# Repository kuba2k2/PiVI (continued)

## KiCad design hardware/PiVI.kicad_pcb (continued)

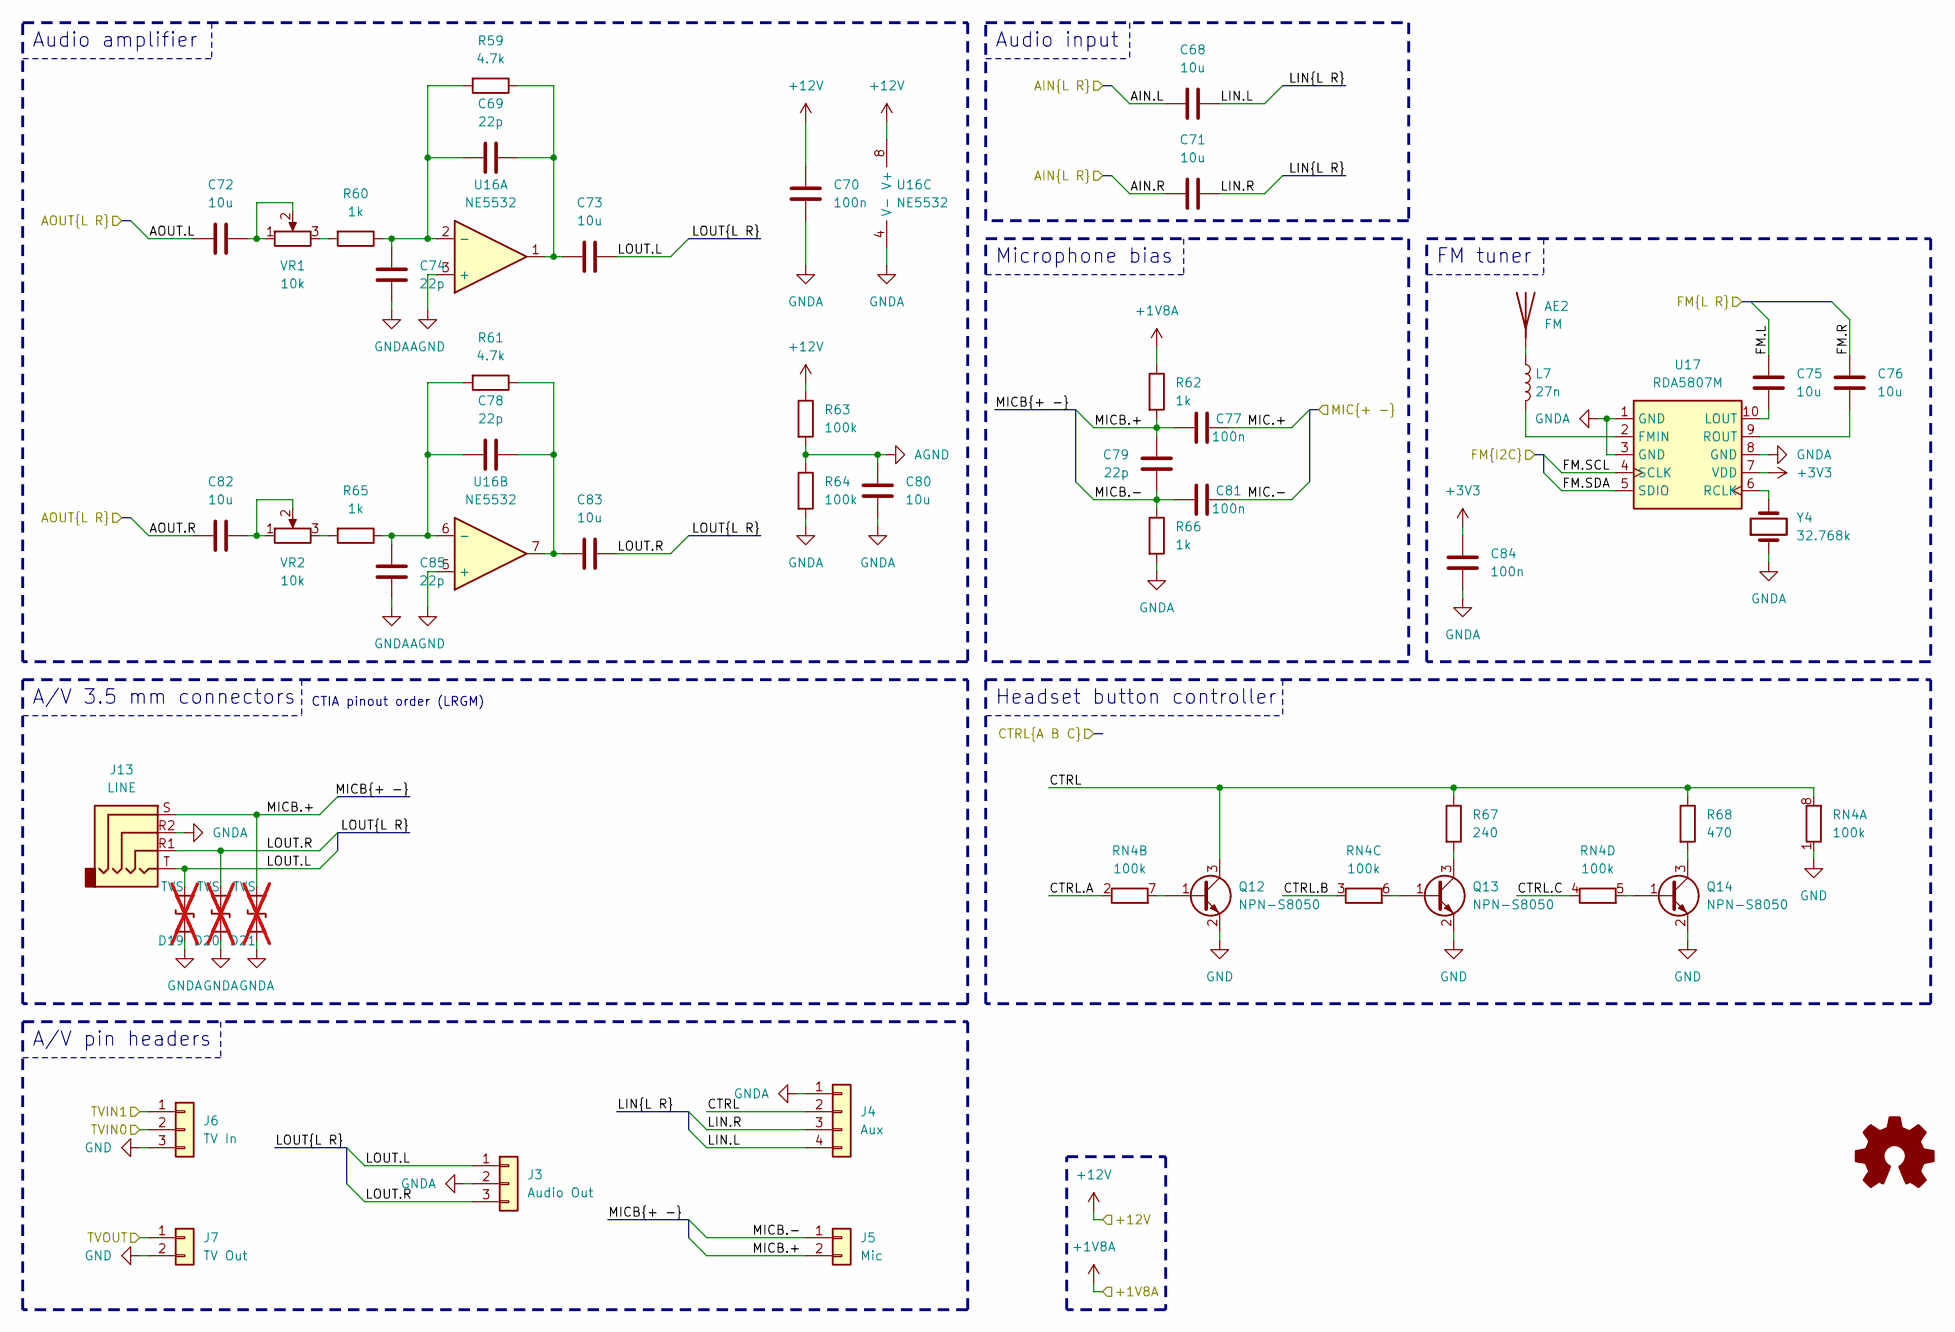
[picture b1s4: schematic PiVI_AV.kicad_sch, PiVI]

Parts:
AE2: FM; TestPoint_Pad_D1.5mm; MPN N/A
C68, C71, C72, C73, C75, C76, C80, C82, C83: 10u; C_0603_1608Metric; MPN C19702
C69, C74, C78, C79, C85: 22p; C_0603_1608Metric; MPN C105620
C70, C77, C81, C84: 100n; C_0603_1608Metric; MPN C14663
D19, D20, D21: TVS; D_SOD-523; MPN C3008120; not fitted
J3: Audio Out; JST_PH_S3B-PH-K_1x03_P2.00mm_Horizontal; MPN C157929
J4: Aux; JST_PH_B4B-PH-K_1x04_P2.00mm_Vertical; MPN C131334
J5: Mic; JST_PH_B2B-PH-K_1x02_P2.00mm_Vertical; MPN C131337
J6: TV In; JST_PH_B3B-PH-K_1x03_P2.00mm_Vertical; MPN C131339
J7: TV Out; JST_PH_B2B-PH-K_1x02_P2.00mm_Vertical; MPN C131337
J13: LINE; Jack_3.5mm_PJ320D_Horizontal; MPN C431535
L7: 27n; L_0603_1608Metric; MPN C12100
Q12, Q13, Q14: NPN-S8050; SOT-23; MPN C181158
R59, R61: 4.7k; R_0603_1608Metric; MPN C2907166
R60, R62, R65, R66: 1k; R_0603_1608Metric; MPN C2907113
R63, R64: 100k; R_0603_1608Metric; MPN C2907088
R67: 240; R_0603_1608Metric; MPN C2907130
R68: 470; R_0603_1608Metric; MPN C2907172
RN4: 100k; R_Array_Convex_4x0603; MPN C173315
U16: NE5532; SOIC-8_3.9x4.9mm_P1.27mm; MPN C7426
U17: RDA5807M; MSOP-10_3x3mm_P0.5mm
VR1, VR2: 10k; Potentiometer_Bourns_3296W_Vertical; MPN C118954
Y4: 32.768k; Crystal_SMD_3215-2Pin_3.2x1.5mm; MPN C5361379

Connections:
+1V8A: R62.1; also elsewhere on the board
+3V3: C84.1, U17.7 (VDD); also elsewhere on the board
+12V: C70.1, R63.1, U16.8 (V+); also elsewhere on the board
/AV/AIN.L: C68.1; also elsewhere on the board
/AV/AIN.R: C71.1; also elsewhere on the board
/AV/AOUT.L: C72.1; also elsewhere on the board
/AV/AOUT.R: C82.1; also elsewhere on the board
/AV/CTRL: J4.2, Q12.3 (C), R67.1, R68.1, RN4.8 (R1.2)
/AV/CTRL.A: RN4.2 (R2.1); also elsewhere on the board
/AV/CTRL.B: RN4.3 (R3.1); also elsewhere on the board
/AV/CTRL.C: RN4.4 (R4.1); also elsewhere on the board
/AV/LIN.L: C68.2, J4.4
/AV/LIN.R: C71.2, J4.3
/AV/LOUT.L: C73.2, D19.1 (A1), J3.1, J13.T
/AV/LOUT.R: C83.2, D20.1 (A1), J3.3, J13.R1
/AV/MIC.+: C77.2; also elsewhere on the board
/AV/MIC.-: C81.2; also elsewhere on the board
/AV/MICB.+: C77.1, C79.1, D21.1 (A1), J5.2, J13.S, R62.2
/AV/MICB.-: C79.2, C81.1, J5.1, R66.1
/FMIN.L: C75.1; also elsewhere on the board
/FMIN.R: C76.1; also elsewhere on the board
/TVIN0: J6.2; also elsewhere on the board
/TVIN1: J6.1; also elsewhere on the board
/TVOUT0: J7.1; also elsewhere on the board
AGND: C80.1, R63.2, R64.1, U16.3 (+), U16.5 (+); also elsewhere on the board
GND: J6.3, J7.2, Q12.2 (E), Q13.2 (E), Q14.2 (E), RN4.1 (R1.1); also elsewhere on the board
GNDA: C70.2, C74.2, C80.2, C84.2, C85.2, D19.2 (A2), D20.2 (A2), D21.2 (A2), J3.2, J4.1, J13.R2, R64.2, R66.2, U16.4 (V-), U17.1 (GND), U17.3 (GND), U17.8 (GND), Y4.1; also elsewhere on the board
unnamed: AE2.1 (A), L7.1
unnamed: C69.2, C73.1, R59.1, U16.1
unnamed: C72.2, VR1.1, VR1.2
unnamed: C78.2, C83.1, R61.1, U16.7
unnamed: C82.2, VR2.1, VR2.2
unnamed: Q12.1 (B), RN4.7 (R2.2)
unnamed: Q13.1 (B), RN4.6 (R3.2)
unnamed: Q13.3 (C), R67.2
unnamed: Q14.1 (B), RN4.5 (R4.2)
unnamed: Q14.3 (C), R68.2
unnamed: R60.2, VR1.3
unnamed: R65.2, VR2.3
unnamed: C69.1, C74.1, R59.2, R60.1, U16.2 (-)
unnamed: C78.1, C85.1, R61.2, R65.1, U16.6 (-)
unnamed: L7.2, U17.2 (FMIN)
unnamed: C75.2, U17.10 (LOUT)
unnamed: U17.6 (RCLK), Y4.2
unnamed: C76.2, U17.9 (ROUT)

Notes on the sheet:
CTIA pinout order (LRGM)
Audio amplifier
Audio input
FM tuner
Headset button controller
A/V 3.5 mm connectors
A/V pin headers
Microphone bias

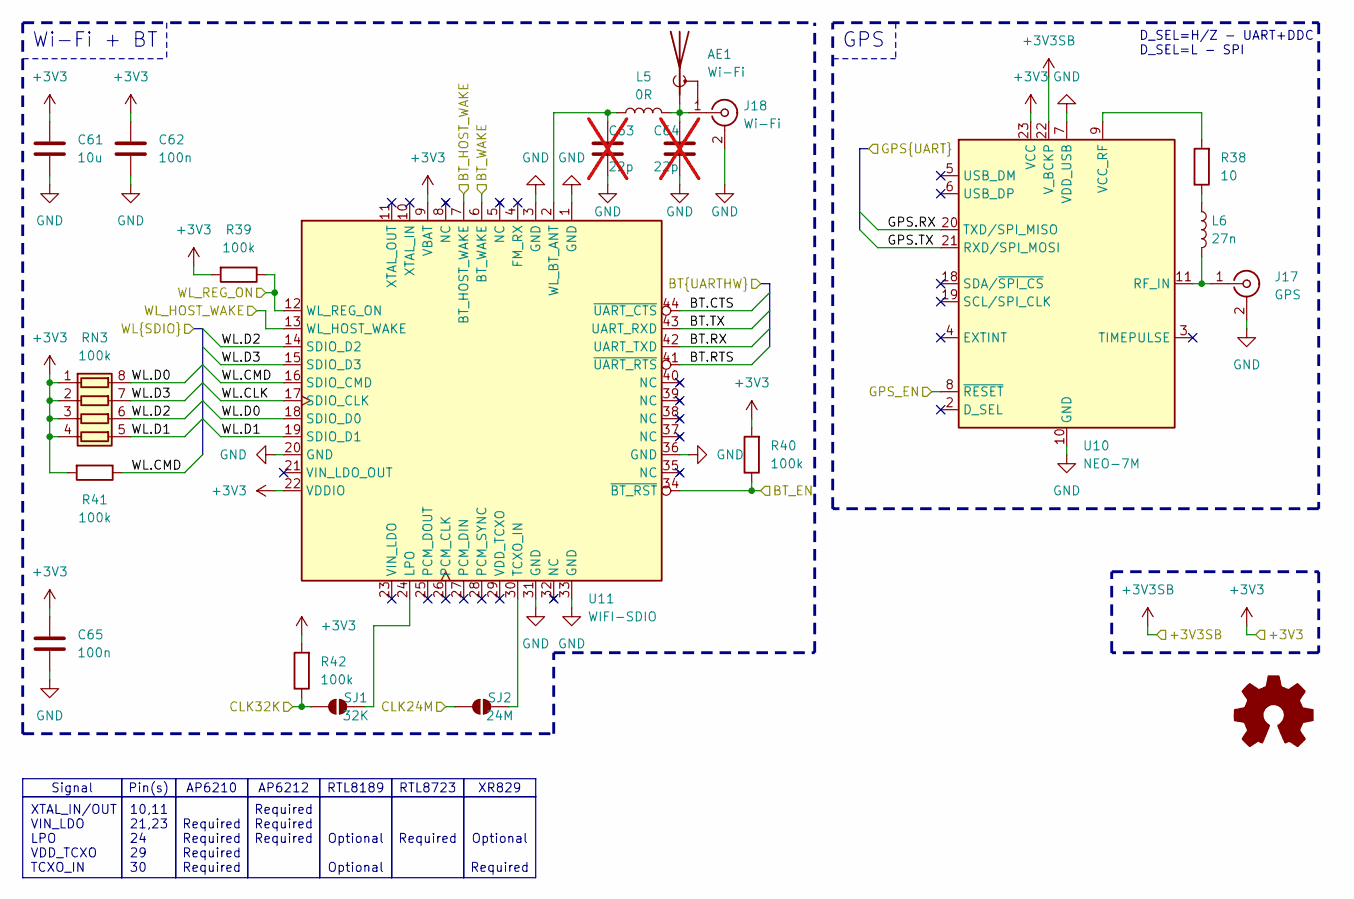
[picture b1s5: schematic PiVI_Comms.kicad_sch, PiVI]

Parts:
AE1: Wi-Fi; Johanson_2450AT18x100; MPN C127629
C61: 10u; C_0603_1608Metric; MPN C19702
C62, C65: 100n; C_0603_1608Metric; MPN C14663
C63, C64: 22p; C_0603_1608Metric; MPN C105620; not fitted
J17: GPS; U.FL_Hirose_U.FL-R-SMT-1_Vertical; MPN C5137195
J18: Wi-Fi; U.FL_Hirose_U.FL-R-SMT-1_Vertical; MPN C5137195
L5: 0R; L_0603_1608Metric
L6: 27n; L_0603_1608Metric; MPN C12100
R38: 10; R_0805_2012Metric; MPN C2907296
R39, R40, R41, R42: 100k; R_0603_1608Metric; MPN C2907088
RN3: 100k; R_Array_Convex_4x0603; MPN C173315
SJ1: 32K; Jumper_2_NO; MPN N/A
SJ2: 24M; Jumper_2_NO; MPN N/A
U10: NEO-7M; ublox_NEO
U11: WIFI-SDIO; WiFi_SDIO_44-pin

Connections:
+3V3: C61.1, C62.1, C65.1, R39.2, R40.2, R41.2, R42.2, RN3.1 (R1.1), RN3.2 (R2.1), RN3.3 (R3.1), RN3.4 (R4.1), U10.23 (VCC), U11.9 (VBAT), U11.22 (VDDIO); also elsewhere on the board
+3V3SB: U10.22 (V_BCKP); also elsewhere on the board
/AP_CLK24M: SJ2.1 (A); also elsewhere on the board
/AP_CLK32K: R42.1, SJ1.1 (A); also elsewhere on the board
/BT.CTS: U11.44 (~UART_CTS); also elsewhere on the board
/BT.RTS: U11.41 (~UART_RTS); also elsewhere on the board
/BT.RX: U11.42 (UART_TXD); also elsewhere on the board
/BT.TX: U11.43 (UART_RXD); also elsewhere on the board
/BT_EN: R40.1, U11.34 (~BT_RST); also elsewhere on the board
/BT_HOST_WAKE: U11.7 (BT_HOST_WAKE); also elsewhere on the board
/BT_WAKE: U11.6 (BT_WAKE); also elsewhere on the board
/GPS.RX: U10.20 (TXD/SPI_MISO); also elsewhere on the board
/GPS.TX: U10.21 (RXD/SPI_MOSI); also elsewhere on the board
/GPS_EN: U10.8 (~RESET); also elsewhere on the board
/WL.CLK: U11.17 (SDIO_CLK); also elsewhere on the board
/WL.CMD: R41.1, U11.16 (SDIO_CMD); also elsewhere on the board
/WL.D0: RN3.8 (R1.2), U11.18 (SDIO_D0); also elsewhere on the board
/WL.D1: RN3.5 (R4.2), U11.19 (SDIO_D1); also elsewhere on the board
/WL.D2: RN3.6 (R3.2), U11.14 (SDIO_D2); also elsewhere on the board
/WL.D3: RN3.7 (R2.2), U11.15 (SDIO_D3); also elsewhere on the board
/WL_HOST_WAKE: U11.13 (WL_HOST_WAKE); also elsewhere on the board
/WL_REG_ON: R39.1, U11.12 (WL_REG_ON); also elsewhere on the board
GND: C61.2, C62.2, C63.1, C64.1, C65.2, J17.2 (Ext), J18.2 (Ext), U10.7 (VDD_USB), U10.10 (GND), U10.12 (GND), U10.13 (GND), U10.24 (GND), U11.1 (GND), U11.3 (GND), U11.20 (GND), U11.31 (GND), U11.33 (GND), U11.36 (GND); also elsewhere on the board
unnamed: AE1.1 (A), C64.2, J18.1 (In), L5.2
unnamed: J17.1 (In), L6.2, U10.11 (RF_IN)
unnamed: L6.1, R38.1
unnamed: SJ1.2 (B), U11.24 (LPO)
unnamed: SJ2.2 (B), U11.30 (TCXO_IN)
unnamed: R38.2, U10.9 (VCC_RF)
unnamed: C63.2, L5.1, U11.2 (WL_BT_ANT)

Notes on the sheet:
RTL8723
AP6210
XR829
Required
Required Required Required Required
Pin(s)
10,11 21,23 24 29 30
Signal
XTAL_IN/OUT VIN_LDO LPO VDD_TCXO TCXO_IN
Required Required Required
AP6212
Optional Required
RTL8189
Optional Optional
Wi-Fi + BT
D_SEL=H/Z - UART+DDC D_SEL=L - SPI
GPS

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
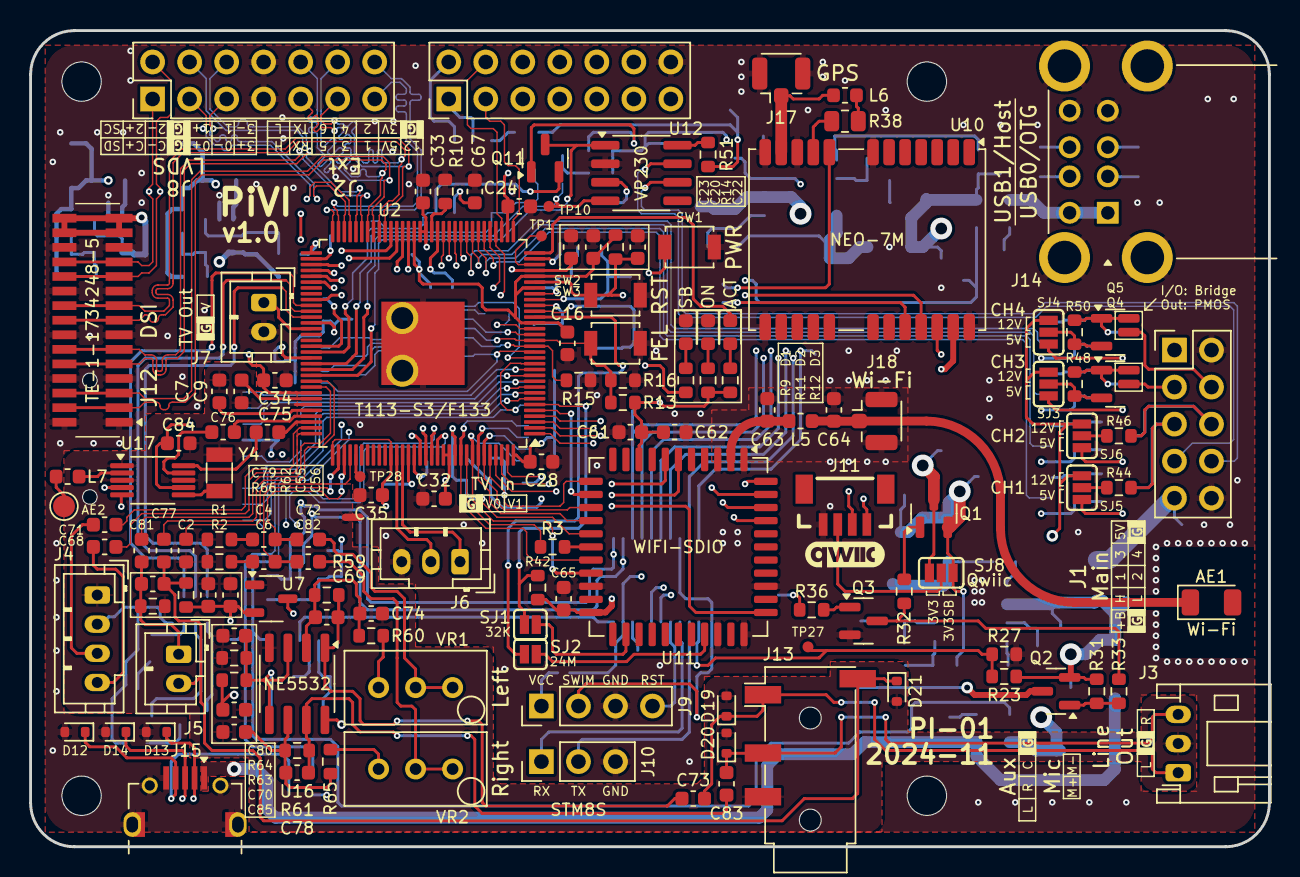
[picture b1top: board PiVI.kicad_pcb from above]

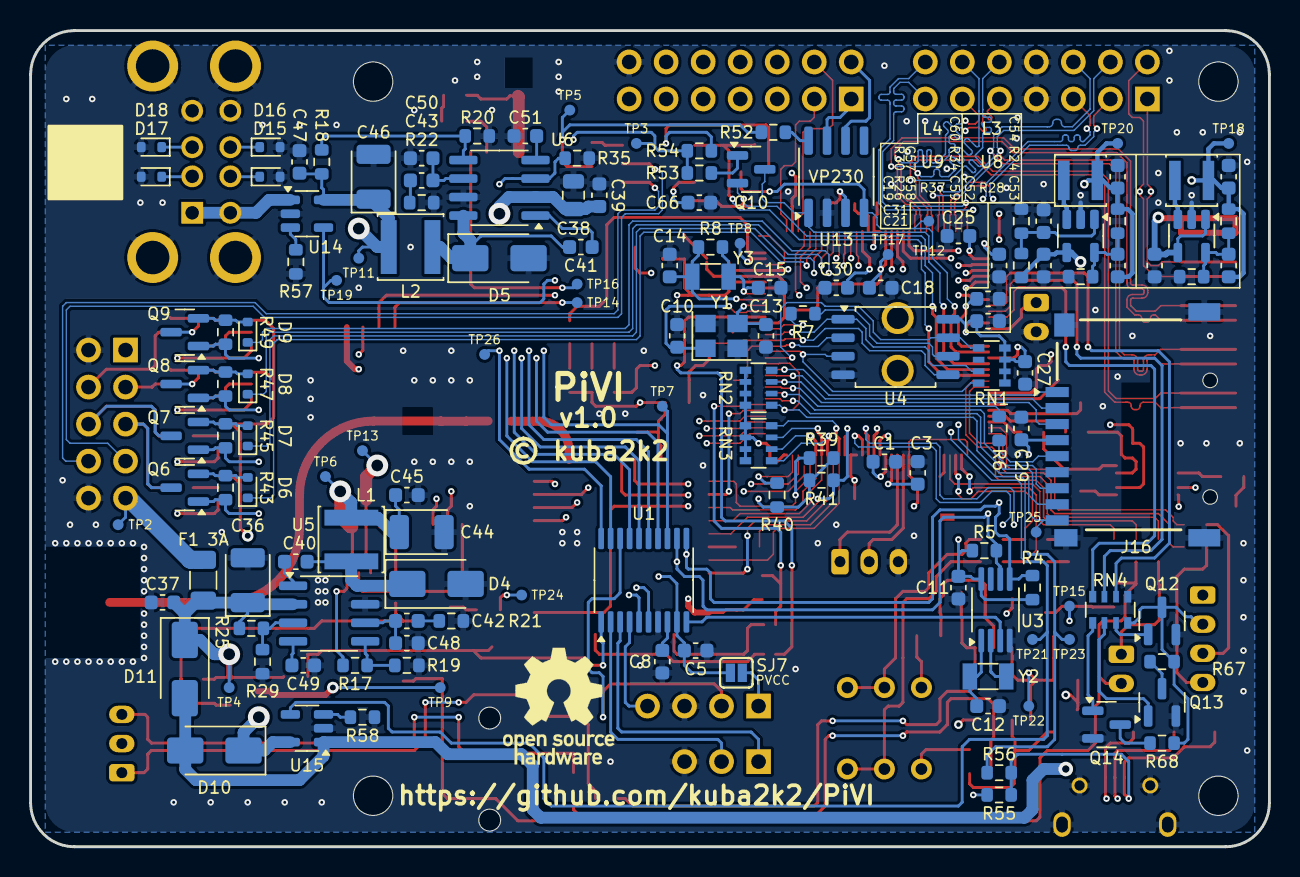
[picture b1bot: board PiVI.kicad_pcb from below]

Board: 4 copper layers, 85.0 x 56.0 mm, 289 parts (147 on the bottom side), 215 nets.

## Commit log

2025-01-29 [hw] Add hardware design files
2025-01-29 [hw] Release v1.0
2025-01-29 Add LICENSE
